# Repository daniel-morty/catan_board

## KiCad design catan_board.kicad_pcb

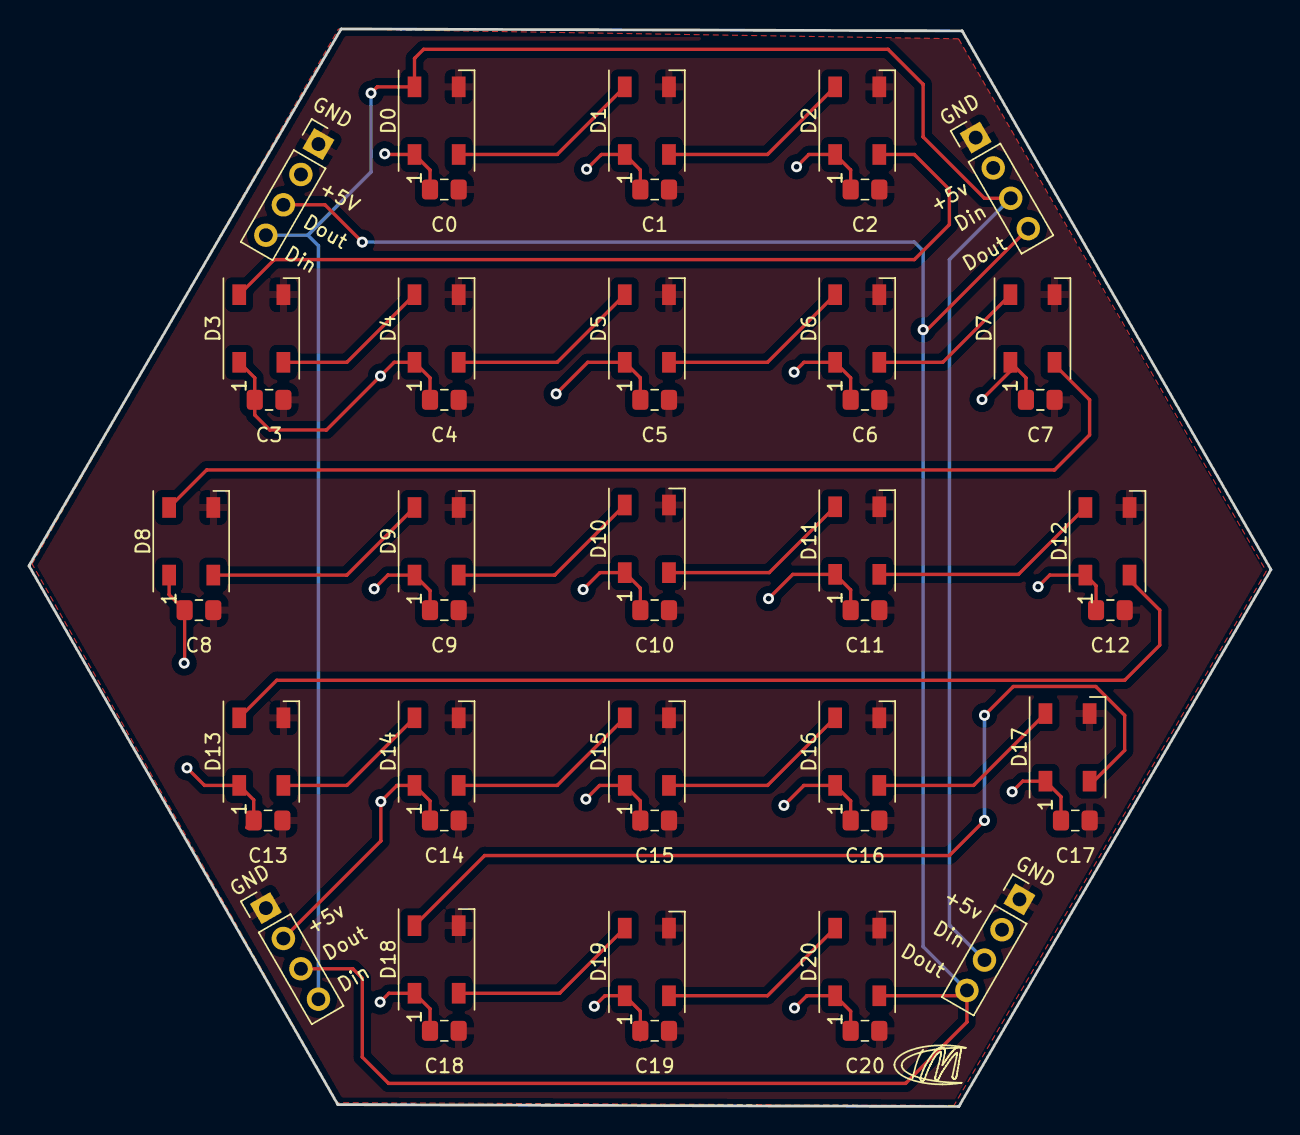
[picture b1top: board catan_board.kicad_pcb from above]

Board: 2 copper layers, 90.0 x 78.1 mm, 46 parts (0 on the bottom side), 24 nets.

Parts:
C0, C1, C2, C3, C4, C5, C6, C7, C8, C9, C10, C11, C12, C13, C14, C15, C16, C17, C18, C19, C20: C_Small; C_0805_2012Metric_Pad1.18x1.45mm_HandSolder
D0, D1, D2, D3, D4, D5, D6, D7, D8, D9, D10, D11, D12, D13, D14, D15, D16, D17, D18, D19, D20: WS2812B; LED_WS2812B_PLCC4_5.0x5.0mm_P3.2mm
GND: PinHeader_1x04_P2.54mm_Vertical
GND#2, GND#3, GND#4: PinHeader_1x04_P2.54mm_Vertical

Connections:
+5V: C0.1, C1.1, C2.1, C3.1, C4.1, C5.1, C6.1, C7.1, C8.1, C9.1, C10.1, C11.1, C12.1, C13.1, C14.1, C15.1, C16.1, C17.1, C18.1, C19.1, C20.1, D0.1, D1.1, D2.1, D3.1, D4.1, D5.1, D6.1, D7.1, D8.1, D9.1, D10.1, D11.1, D12.1, D13.1, D14.1, D15.1, D16.1, D17.1, D18.1, D19.1, D20.1, GND.2, GND#2.2, GND#3.2, GND#4.2
GND: C0.2, C1.2, C2.2, C3.2, C4.2, C5.2, C6.2, C7.2, C8.2, C9.2, C10.2, C11.2, C12.2, C13.2, C14.2, C15.2, C16.2, C17.2, C18.2, C19.2, C20.2, D0.3, D1.3, D2.3, D3.3, D4.3, D5.3, D6.3, D7.3, D8.3, D9.3, D10.3, D11.3, D12.3, D13.3, D14.3, D15.3, D16.3, D17.3, D18.3, D19.3, D20.3, GND.1, GND#2.1, GND#3.1, GND#4.1
unnamed: D0.2, D1.4
unnamed: D0.4, GND.4, GND#2.4, GND#3.3, GND#4.3
unnamed: D1.2, D2.4
unnamed: D2.2, D3.4
unnamed: D3.2, D4.4
unnamed: D4.2, D5.4
unnamed: D5.2, D6.4
unnamed: D6.2, D7.4
unnamed: D7.2, D8.4
unnamed: D8.2, D9.4
unnamed: D10.2, D11.4
unnamed: D9.2, D10.4
unnamed: D11.2, D12.4
unnamed: D12.2, D13.4
unnamed: D13.2, D14.4
unnamed: D14.2, D15.4
unnamed: D15.2, D16.4
unnamed: D16.2, D17.4
unnamed: D17.2, D18.4
unnamed: D18.2, D19.4
unnamed: D19.2, D20.4
unnamed: D20.2, GND.3, GND#2.3, GND#3.4, GND#4.4

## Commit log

2022-03-03 netlist generated
2022-03-29 gnd pour done, maybe should add 5v rail on other side
2022-03-29 5v rail added to back copper
2022-04-14 pcb is done
2022-07-23 its been a while
2022-07-23 change ports to header pins
2022-07-23 add gerber, pcb ordered
2022-08-26 moving software files
